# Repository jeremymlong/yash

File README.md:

# YASH (Yet another sample and hold)
[Original project](https://www.schmitzbits.de/sah.html) by Rene Schmitz.

<table>
    <tr>
        <td></td>
        <td></td>
        <td></td>
    </tr>
</table>

# Stats
- 4HP

# BOM
| Part | Quantity | Link |
|----|----|----|
| CD4093 | 1 | [Tayda](https://www.taydaelectronics.com/cd4093-4093-ic-cmos-nand-schmitt-trigger.html) |
| LF398 | 1 | [ebay](https://www.ebay.com/itm/123885878582) |
| 2N3904 | 1 | [Tayda](https://www.taydaelectronics.com/2n3904-npn-general-propose-transistor.html) |
| 1N4148 | 1 | [Tayda](https://www.taydaelectronics.com/1n4148-switching-signal-diode.html) |
| LED | 1 | [Tayda](https://www.taydaelectronics.com/led-5mm-red.html) |
| 470pF cap | 1 | [Tayda](https://www.taydaelectronics.com/470pf-100v-ceramic-disc-capacitor-pkg-of-10-aec.html) |
| 1nF cap | 1 | [Tayda](https://www.taydaelectronics.com/1nf-0-001uf-100v-5-polyester-film-box-type-capacitor.html) |
| 100nF cap | 2 | [Tayda](https://www.taydaelectronics.com/0-1uf-100v-5-polyester-film-box-type-capacitor.html) |
| 470nF cap | 1 | [Tayda](https://www.taydaelectronics.com/0-47uf-100v-5-polyester-film-box-type-capacitor.html) |
| 10uF cap | 2 | [Tayda](https://www.taydaelectronics.com/10uf-50v-105c-radial-electrolytic-capacitor-5x11mm.html) |
| Mono audio jack | 3 | [Tayda](https://www.taydaelectronics.com/pj-3001f-3-5-mm-mono-phone-jack.html) |
| Power box header | 1 | [Tayda](https://www.taydaelectronics.com/10-pin-box-header-connector-2-54mm.html) |
| 1M Pot | 1 | [Tayda](https://www.taydaelectronics.com/1m-ohm-linear-taper-potentiometer-round-shaft-pcb-9mm.html) |
| 1k   | 1 | [Tayda](https://www.taydaelectronics.com/10-x-resistor-1k-ohm-1-4w-1-metal-film-pkg-of-10.html) |
| 1.8k | 1 | [Tayda](https://www.taydaelectronics.com/resistor-1-8k-ohm-1-4w-1-metal-film-pkg-of-10.html) |
| 2.2k | 1 | [Tayda](https://www.taydaelectronics.com/resistor-2-2k-ohm-1-4w-1-metal-film-pkg-of-10.html) |
| 4.7k | 1 | [Tayda](https://www.taydaelectronics.com/10-x-resistor-4-7k-ohm-1-4w-1-metal-film-pkg-of-10.html) |
| 5.6k | 1 | [Tayda](https://www.taydaelectronics.com/10-x-resistor-5-6k-ohm-1-4w-1-metal-film-pkg-of-10.html) |
| 10k  | 1 | [Tayda](https://www.taydaelectronics.com/10-x-resistor-10k-ohm-1-4w-1-metal-film-pkg-of-10.html) |
| 100k | 1 | [Tayda](https://www.taydaelectronics.com/10-x-resistor-100k-ohm-1-4w-1-metal-film-pkg-of-10.html) |

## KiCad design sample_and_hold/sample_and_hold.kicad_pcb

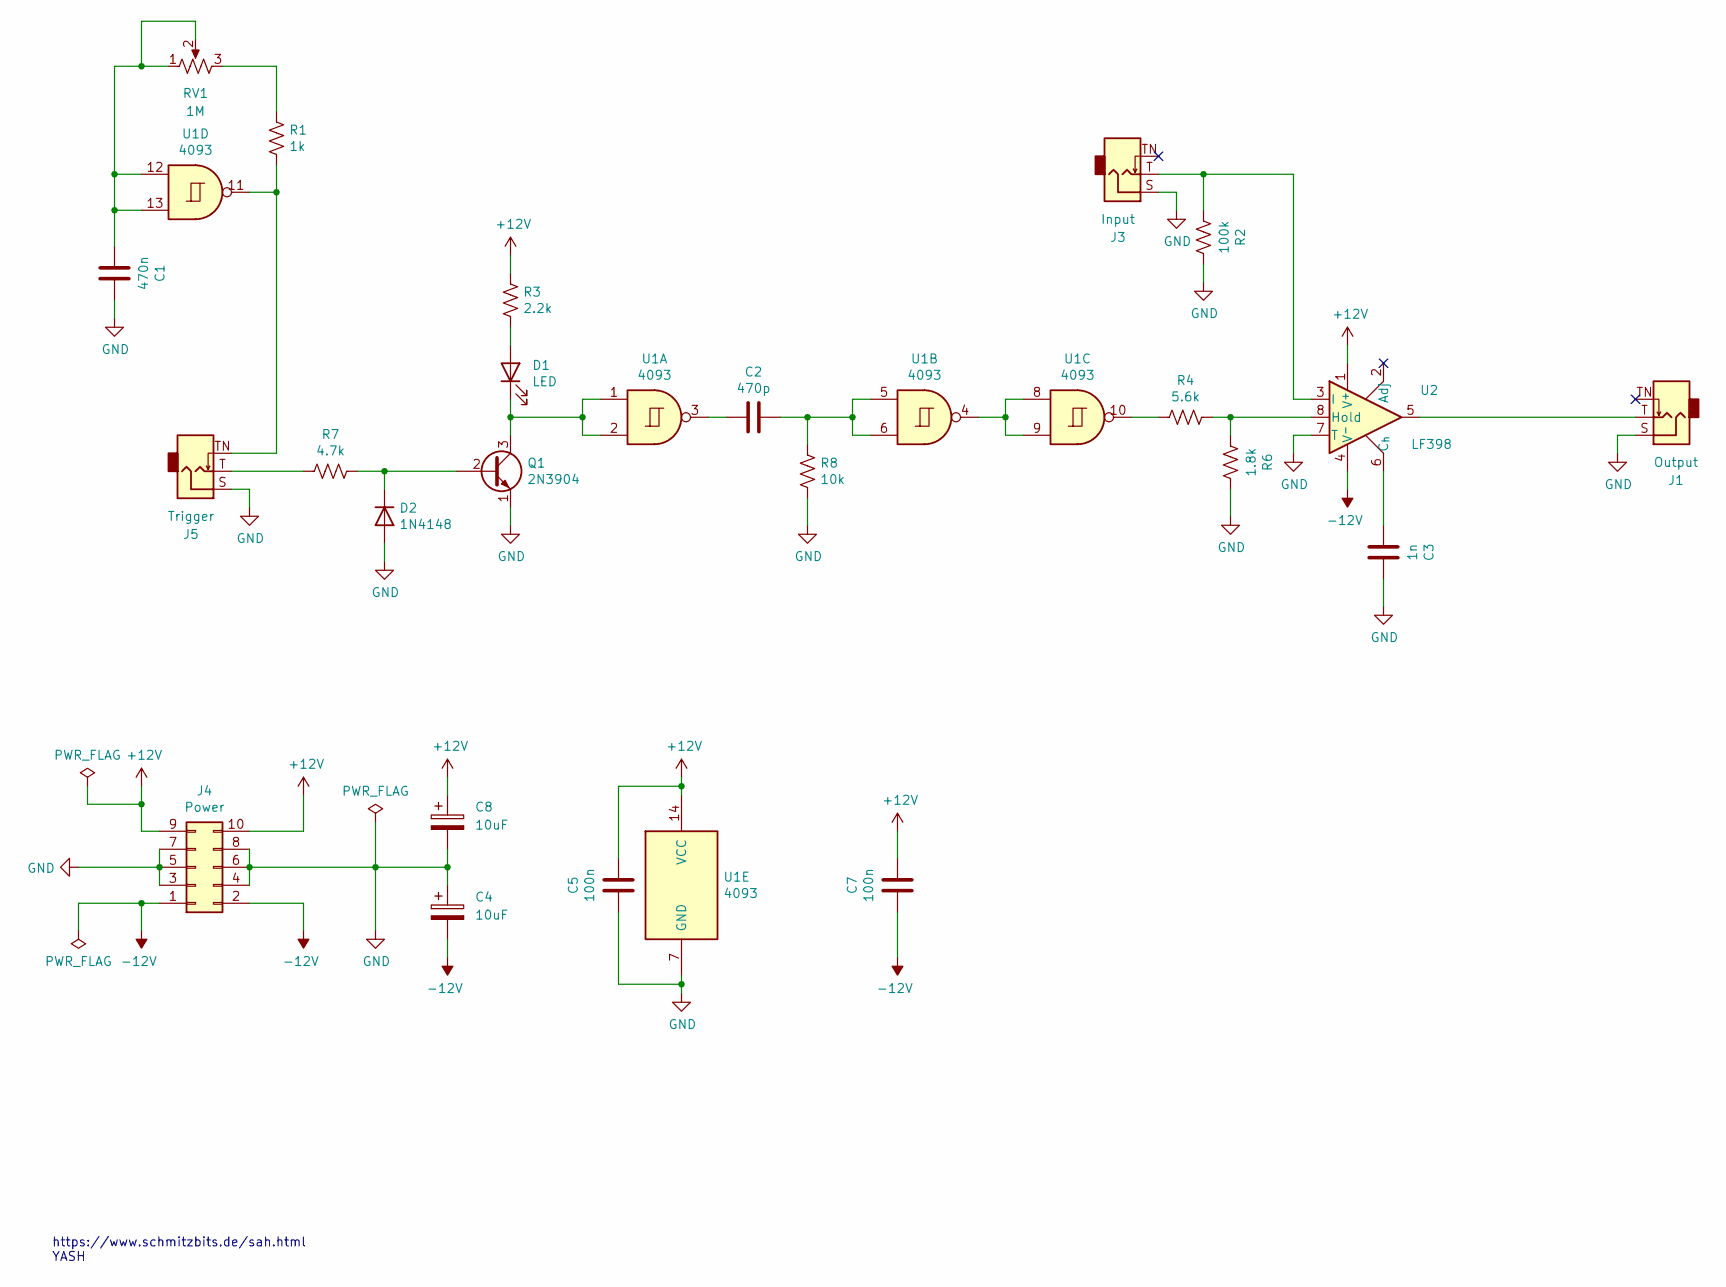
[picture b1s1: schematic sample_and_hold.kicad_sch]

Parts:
C1: 470n; C_Rect_L7.0mm_W3.5mm_P5.00mm
C2: 470p; C_Rect_L7.0mm_W3.5mm_P5.00mm
C3: 1n; C_Rect_L7.0mm_W3.5mm_P5.00mm
C4, C8: 10uF; CP_Radial_D5.0mm_P2.00mm
C5, C7: 100n; C_Rect_L7.0mm_W3.5mm_P5.00mm
D1: LED; LED_D5.0mm
D2: 1N4148; D_DO-35_SOD27_P7.62mm_Horizontal
J1: Output; Jack_3.5mm_QingPu_WQP-PJ398SM_Vertical_CircularHoles
J3: Input; Jack_3.5mm_QingPu_WQP-PJ398SM_Vertical_CircularHoles
J4: Power; IDC-Header_2x05_P2.54mm_Vertical
J5: Trigger; Jack_3.5mm_QingPu_WQP-PJ398SM_Vertical_CircularHoles
Q1: 2N3904; TO-92_Inline
R1: 1k; R_Axial_DIN0207_L6.3mm_D2.5mm_P7.62mm_Horizontal
R2: 100k; R_Axial_DIN0207_L6.3mm_D2.5mm_P7.62mm_Horizontal
R3: 2.2k; R_Axial_DIN0207_L6.3mm_D2.5mm_P7.62mm_Horizontal
R4: 5.6k; R_Axial_DIN0207_L6.3mm_D2.5mm_P7.62mm_Horizontal
R6: 1.8k; R_Axial_DIN0207_L6.3mm_D2.5mm_P7.62mm_Horizontal
R7: 4.7k; R_Axial_DIN0207_L6.3mm_D2.5mm_P7.62mm_Horizontal
R8: 10k; R_Axial_DIN0207_L6.3mm_D2.5mm_P7.62mm_Horizontal
RV1: 1M; Potentiometer_Alpha_RD901F-40-00D_Single_Vertical
U1: 4093; DIP-14_W7.62mm_Socket
U2: LF398; DIP-8_W7.62mm_Socket

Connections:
+12V: C5.1, C7.1, C8.1, J4.9, J4.10, R3.2, U1.14 (VCC), U2.1 (V^{+})
-12V: C4.2, C7.2, J4.1, J4.2, U2.4 (V^{-})
GND: C1.1, C3.1, C4.1, C5.2, C8.2, D2.2 (A), J1.S, J3.S, J4.3, J4.4, J4.5, J4.6, J4.7, J4.8, J5.S, Q1.1 (E), R2.1, R6.1, R8.1, U1.7 (GND), U2.7 (T)
unnamed: C1.2, RV1.1, RV1.2, U1.12, U1.13
unnamed: C2.1, R8.2, U1.5, U1.6
unnamed: C2.2, U1.3
unnamed: D1.2 (A), R3.1
unnamed: D1.1 (K), Q1.3 (C), U1.1, U1.2
unnamed: D2.1 (K), Q1.2 (B), R7.1
unnamed: J1.T, U2.5
unnamed: J5.T, R7.2
unnamed: J5.TN, R1.1, U1.11
unnamed: R1.2, RV1.3
unnamed: R4.2, U1.10
unnamed: U1.4, U1.8, U1.9
unnamed: C3.2, U2.6 (C_{h})
unnamed: R4.1, R6.2, U2.8 (Hold)
unnamed: J3.T, R2.2, U2.3 (I)

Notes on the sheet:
https://www.schmitzbits.de/sah.html YASH

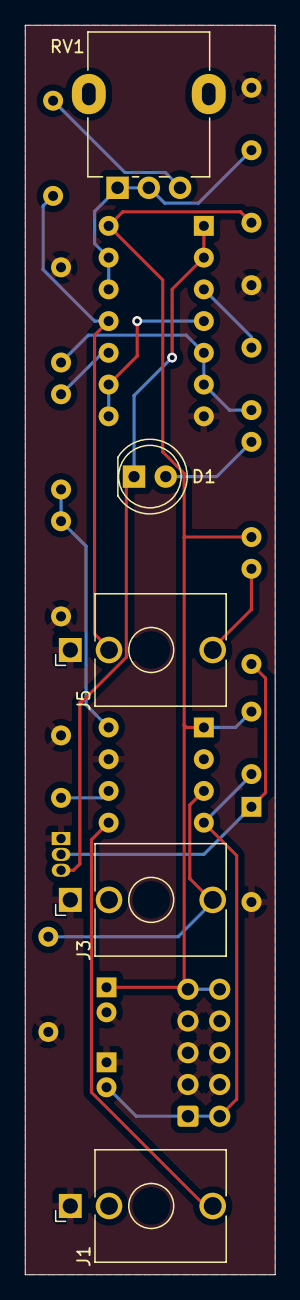
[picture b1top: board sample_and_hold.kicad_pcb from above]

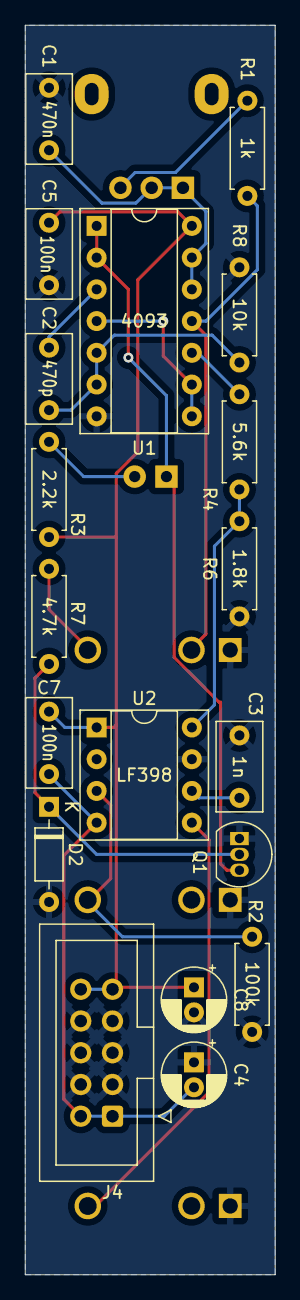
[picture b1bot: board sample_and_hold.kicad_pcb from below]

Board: 2 copper layers, 20.0 x 100.0 mm, 24 parts (19 on the bottom side), 18 nets.

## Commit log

2024-04-15 README update, images
2024-04-15 Images in table
2024-04-15 Ditched table
